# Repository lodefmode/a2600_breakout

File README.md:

# a2600_breakout

Simple PCB to expose all cartridge lines on an Atari 2600.

Features:

<ul>
 <li>Multiple access points for all data and address lines
 <br>(Example: connect duplicate headers for both logic analyzer + breadboarding)
 <li>Optional cartridge connector for live monitoring
 <br>(Connect either a right angle socket connector or solder directly to top edges)</li>
 <li>Standard 0.1" spacing throughout</li>
 <li>GND and VDD points</li>
 <li>Fully labelled on both sides</li>
 <li>Ground plane</li>
 <li>Unlicenced / Public Domain
</ul>

For inquires please contact:

lodef.mode@gmail.com

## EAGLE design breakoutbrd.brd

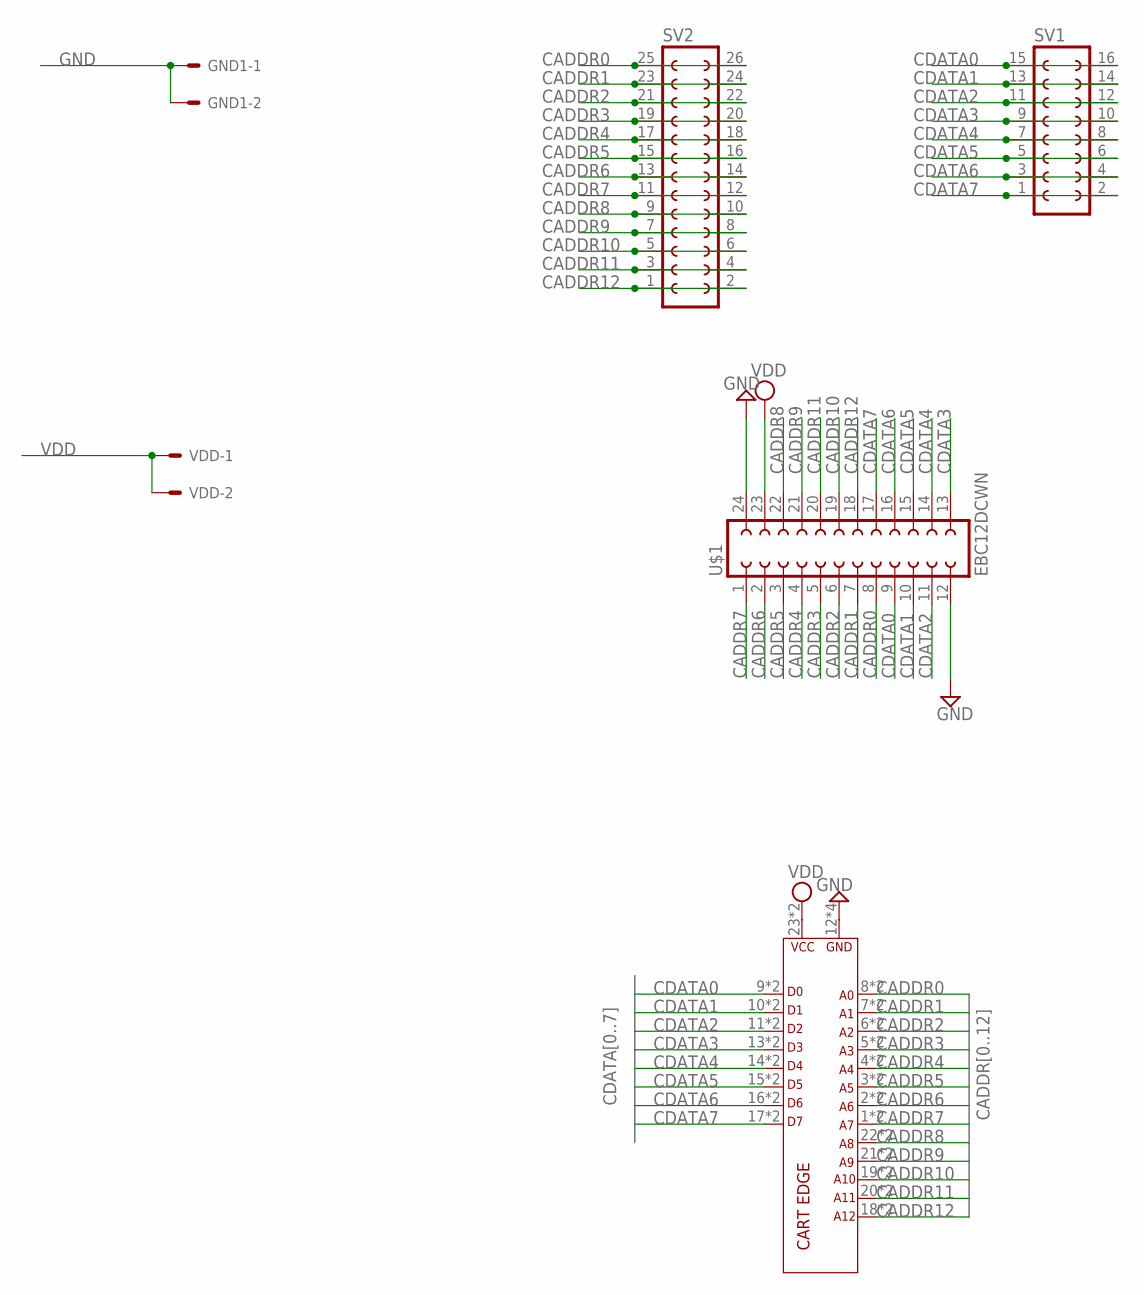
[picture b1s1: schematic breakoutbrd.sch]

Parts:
GND1: 22-23-2021
J1: ATARI-2600; BREAKOUT_BOARD
SV1: FE08-2
SV2: FE13-2
U$1: EBC12DCWN
VDD: 22-23-2021

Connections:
CADDR0: J1.8 (A0), J1.32 (A0), SV2.25, SV2.26, U$1.8
CADDR1: J1.7 (A1), J1.31 (A1), SV2.23, SV2.24, U$1.7
CADDR2: J1.6 (A2), J1.30 (A2), SV2.21, SV2.22, U$1.6
CADDR3: J1.5 (A3), J1.29 (A3), SV2.19, SV2.20, U$1.5
CADDR4: J1.4 (A4), J1.28 (A4), SV2.17, SV2.18, U$1.4
CADDR5: J1.3 (A5), J1.27 (A5), SV2.15, SV2.16, U$1.3
CADDR6: J1.2 (A6), J1.26 (A6), SV2.13, SV2.14, U$1.2
CADDR7: J1.1 (A7), J1.25 (A7), SV2.11, SV2.12, U$1.1
CADDR8: J1.22 (A8), J1.46 (A8), SV2.9, SV2.10, U$1.22
CADDR9: J1.21 (A9), J1.45 (A9), SV2.7, SV2.8, U$1.21
CADDR10: J1.19 (A10), J1.43 (A10), SV2.5, SV2.6, U$1.19
CADDR11: J1.20 (A11), J1.44 (A11), SV2.3, SV2.4, U$1.20
CADDR12: J1.18 (A12), J1.42 (A12), SV2.1, SV2.2, U$1.18
CDATA0: J1.9 (D0), J1.33 (D0), SV1.15, SV1.16, U$1.9
CDATA1: J1.10 (D1), J1.34 (D1), SV1.13, SV1.14, U$1.10
CDATA2: J1.11 (D2), J1.35 (D2), SV1.11, SV1.12, U$1.11
CDATA3: J1.13 (D3), J1.37 (D3), SV1.9, SV1.10, U$1.13
CDATA4: J1.14 (D4), J1.38 (D4), SV1.7, SV1.8, U$1.14
CDATA5: J1.15 (D5), J1.39 (D5), SV1.5, SV1.6, U$1.15
CDATA6: J1.16 (D6), J1.40 (D6), SV1.3, SV1.4, U$1.16
CDATA7: J1.17 (D7), J1.41 (D7), SV1.1, SV1.2, U$1.17
GND: GND1.1, GND1.2, J1.12 (GND), J1.24 (GND), J1.36 (GND), J1.48 (GND), U$1.12, U$1.24
VDD: J1.23 (VCC), J1.47 (VCC), U$1.23, VDD.1, VDD.2

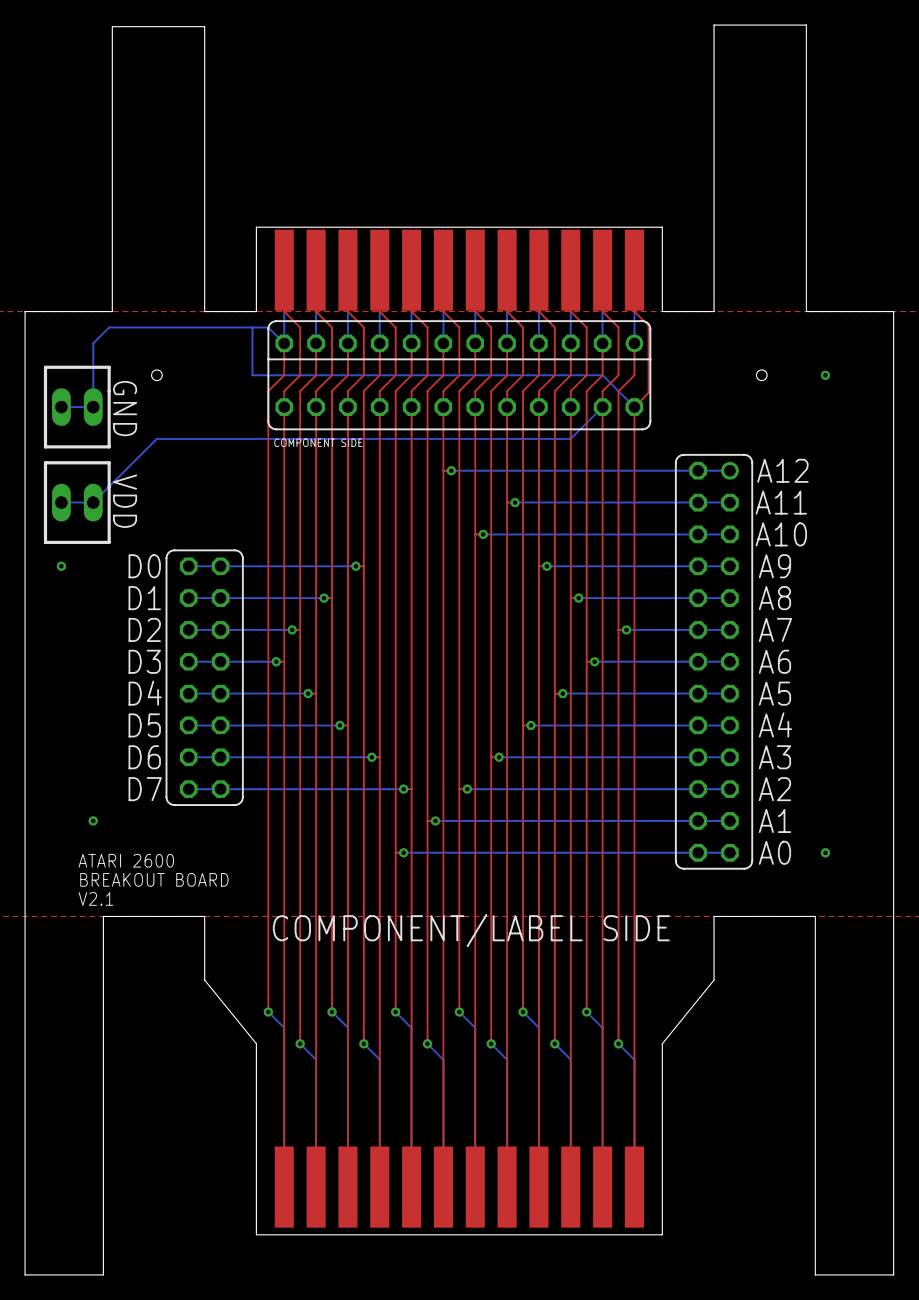
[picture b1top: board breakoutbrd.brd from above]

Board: 2 copper layers, 69.3 x 99.7 mm, 6 parts (1 on the bottom side), 23 nets.

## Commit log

2022-01-19 Formatting readme
2022-01-20 Moved all components to land on 0.1" spacing, even between components. Makes soldering of all pins over a breadboard possible.
2022-01-20 updated image for latest revision.
2022-01-20 missing library
2022-01-21 added female 26-pin cart connector: EBC12DCWN
2022-01-21 optional cartridge connector added to pcb
2022-01-21 Updated features
2022-01-30 Upright cartridge connector, work in progress
2022-01-30 More adjustments
2022-01-31 working on double sided edge connectors, work in progrss.
2022-01-31 more layout work
2022-02-02 spread out vias grouped VDD and GND points on same side better labeling
2022-02-03 Cartridge extension, prongs measured.
2022-02-03 Image back to jpeg format.
2022-02-03 changed feature list
2022-02-05 more accurate prong lengths
2022-02-22 shorten top edges set VDD on 0.1 interval
2022-02-22 updated docs
2022-02-22 better docs
